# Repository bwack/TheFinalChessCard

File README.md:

# TheFinalChessCard Replica

TheFinalChessCard for C64/C128, replicated using SprintLayout. Here are the sprint and gerber files.

The scanned images are from the World of Jani blog article about this card. See also the forum64.de threads.
- http://blog.worldofjani.com/?p=3460
- https://www.forum64.de/index.php?thread/73757-the-final-chesscard/

## preview images from SprintLayout

# The Replica 1.0 prototype

The PCB Rev 1.0 has been [prototyped by Amon_RA on twitter](https://twitter.com/Amon_RA/status/1220659582181224448 "The tweets"). Thank you so much! Here are two images from his setup:

Image 1            |  Image 2
:-------------------------:|:-------------------------:
  |  

The Rev 1.0 had a grounded READ pin near the top edge. To find it look at the 74LS32 closest to the CPU, pin 8. If you have Rev 1.0, cut this trace betwen pin8 and GND at top edge. This is fixed in Rev 1.1

I would also like to thank the work by lvr for the schematics draft he posted in [a forum64.de thread](https://www.forum64.de/index.php?thread/73757-the-final-chesscard/&postID=1139564#post1139564 "A draft of the schematics for TheFinalChessCart"). With this schematic I was able to match my gerbers against a netlist generated from his schematics, and in this way the error in Rev 1.0 was easy to spot. The draft was very close to the layout. Thanks also to [@thilographie_de](https://twitter.com/thilographie_de) for hunting the error with me.

# Links

After doing the C64 KU-motherboard and the videoseries, I still hadn't shown my viewers how I went from images to gerber files. This is where I got the motivation for doing this TFCC replica. I made two videos. The first video got linked on Jani's website and also ended up in an article about it on hackaday called [Reverse Engineer PCBs With SprintLayout](https://hackaday.com/2019/12/31/reverse-engineer-pcbs-with-sprintlayout/). :-)

## Change log

* 2020-01-25 Rev 1.1:
  * pin 8 "READ" on 74LS32 (near CPU) was grounded. Removed GND.
  * A trace stopped too early before a via. Still connected. Fixed.
* 2019-12-31 Rev 1.0: Touched up traces on a finer grid. 45degree bends.
* shown in video: traced up. quick 90 degree bends

# TheFinalChessCard KiCad (modified replica)

The replica above I'd like to be .. a replica. Some changes are desired.
In this KiCad version we have moved two ICs back onto the grid. They were just too close for IC sockets.
A zener diode was also too close to the same ICs. The crystal touched some metal. The power rails were thin.
I have solved the changes in this version.
The schematics were drafted by lvr as mentioned above regarding the PCB Rev 1.0.

Gerbers are available. Look under the KiCad folder.

## Change log
The KiCad version branches off from the replica 1.1 board, hence why it is called 1.1.K1 where K is KiCad :)

Note that this version has never been prototype. Use at own risk if you decide to do so!

* 2020-01-26 Rev 1.1.K1:
  * Silkscreen artwork
  * Thicker power traces (0.63. -> 1mm)
  * Better space between two ICs. Moved some components to satisfy Cortyard errors.
  * New reset button. Standard 5x5mm push button.

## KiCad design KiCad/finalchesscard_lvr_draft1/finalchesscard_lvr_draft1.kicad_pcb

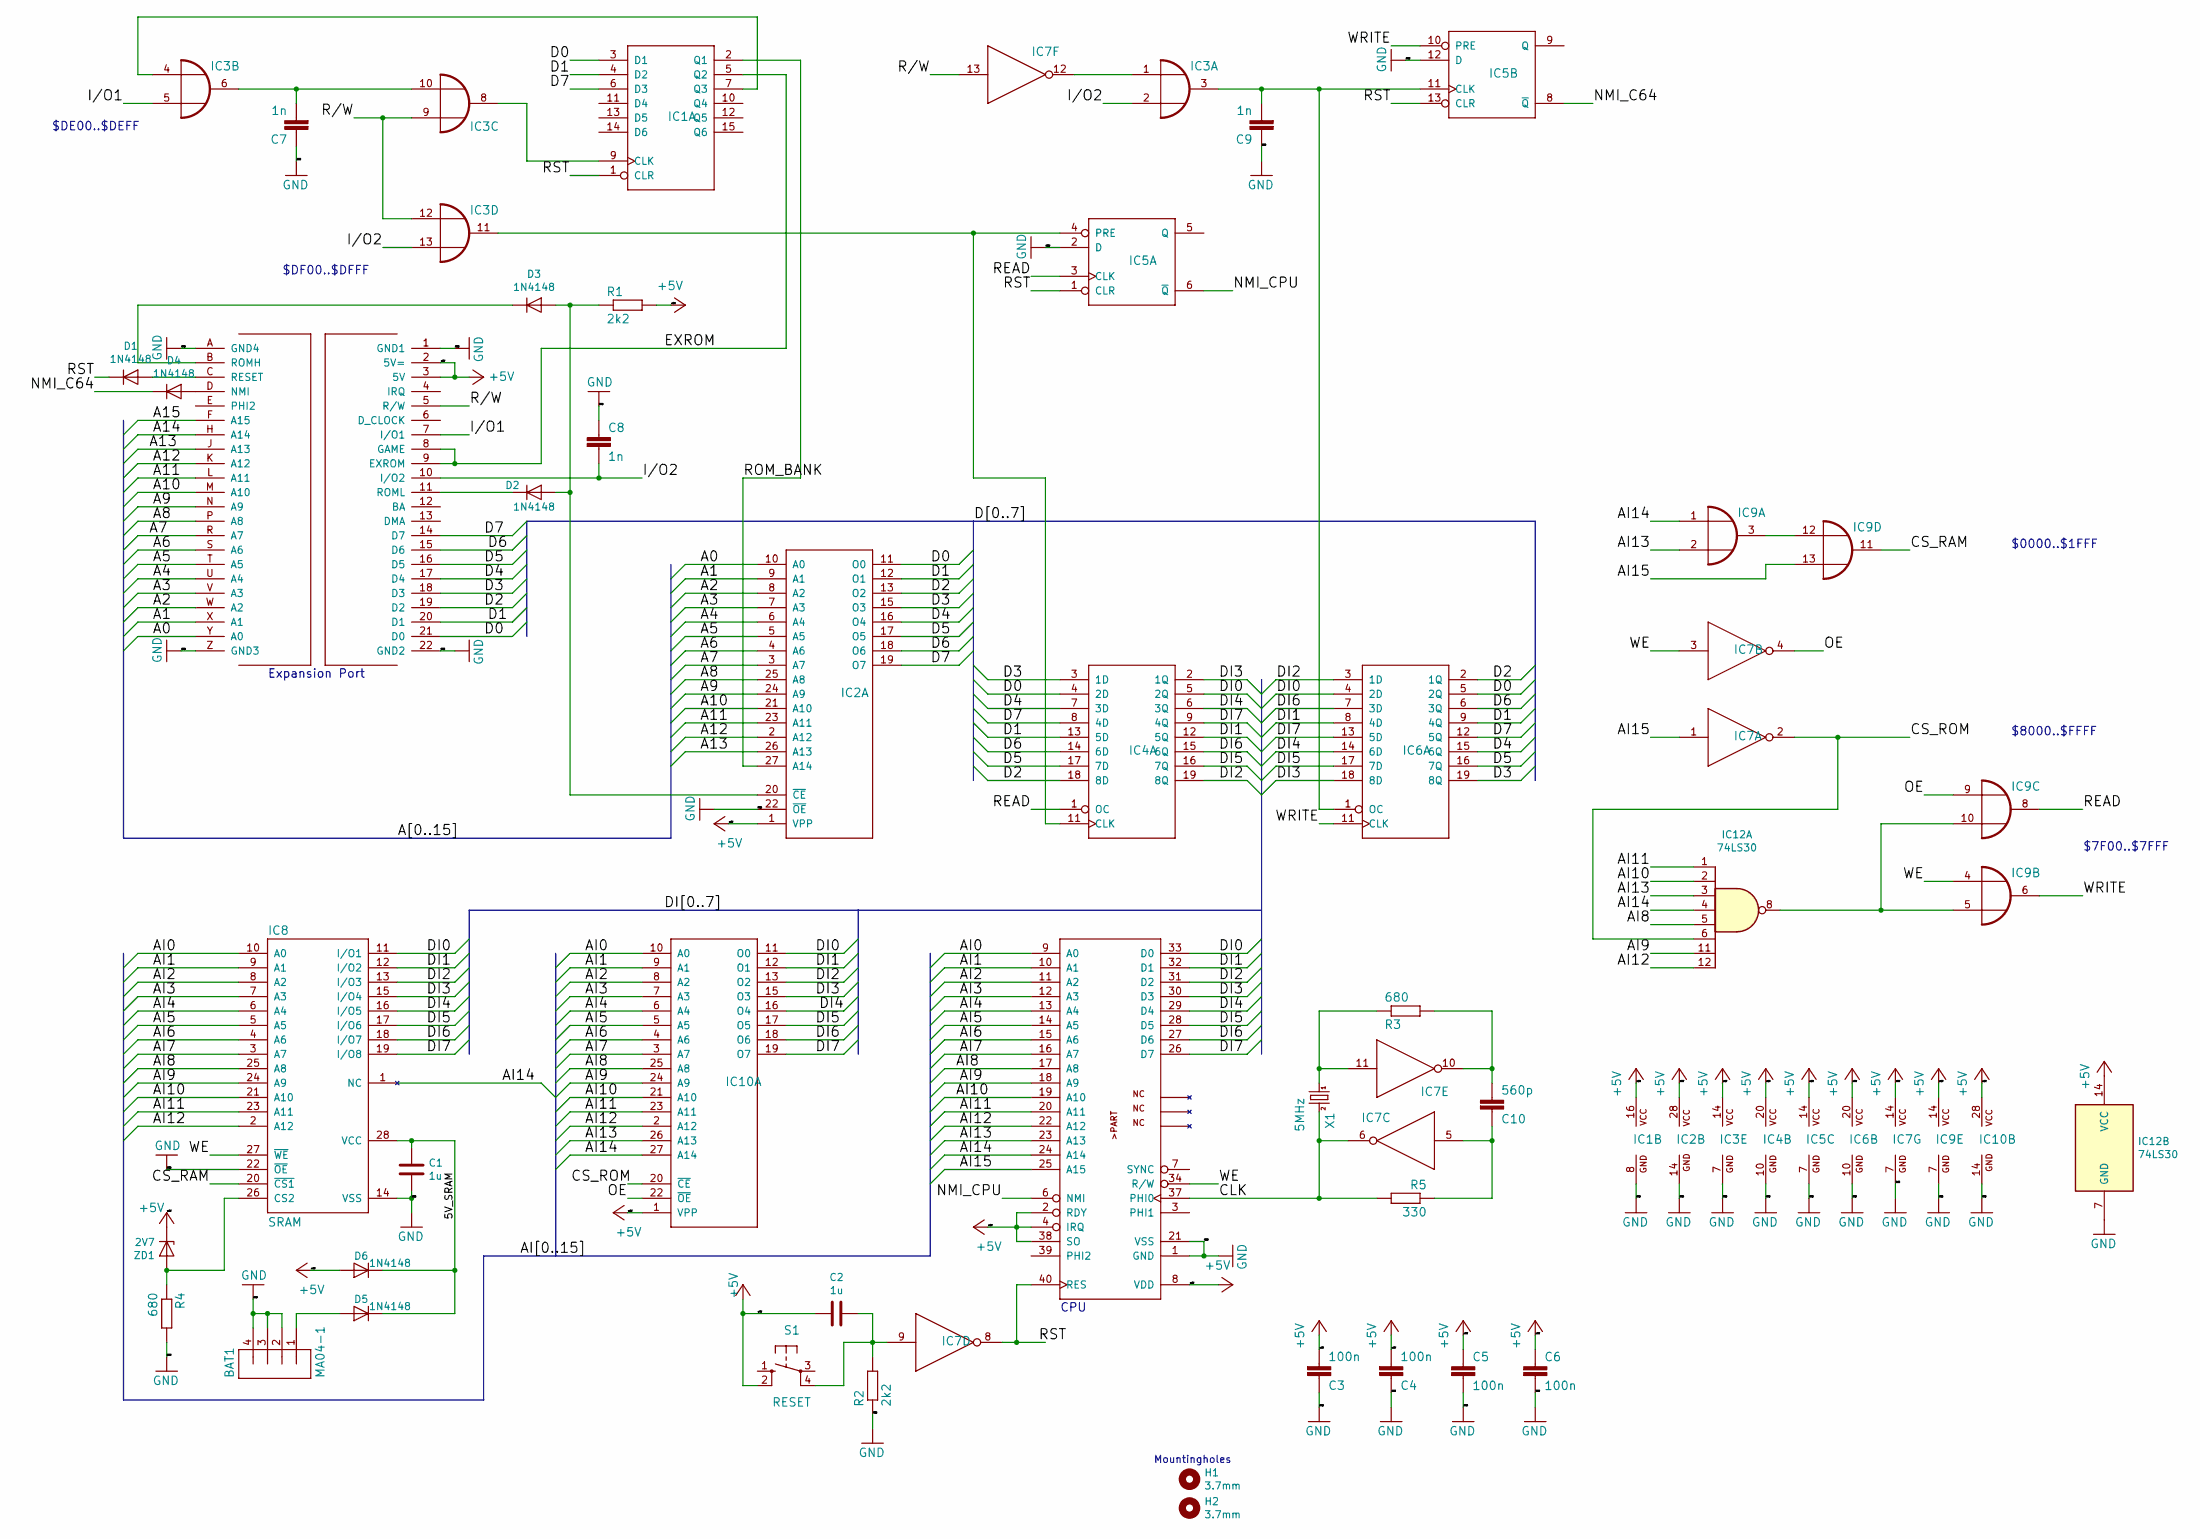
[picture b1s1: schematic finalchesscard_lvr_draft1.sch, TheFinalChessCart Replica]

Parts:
BAT1: MA04-1; PinHeader_1x04_P2.54mm_Vertical
C1: 1u; C_Rect_L7.0mm_W2.0mm_P5.00mm
C2: 1u; C_Rect_L4.0mm_W2.5mm_P2.50mm
C3, C4, C5, C6: 100n; C_Disc_D4.3mm_W1.9mm_P5.00mm
C7, C8, C9: 1n; C_Disc_D4.3mm_W1.9mm_P5.00mm
C10: 560p; C_Disc_D4.3mm_W1.9mm_P5.00mm
D1, D2, D3, D4: 1N4148; D_DO-34_SOD68_P10.16mm_Horizontal
D5, D6: 1N4148; D_DO-34_SOD68_P7.62mm_Horizontal
H1, H2: 3.7mm; MountingHole_3.7mm
IC1: 74174N; DIP-16_W7.62mm
IC2: ROM1; DIP-28_W15.24mm
IC3, IC9: 7432N; DIP-14_W7.62mm
IC4, IC6: 74374N; DIP-20_W7.62mm
IC5: 7474N; DIP-14_W7.62mm
IC7: 74LS04N; DIP-14_W7.62mm
IC8: SRAM; DIP-28_W15.24mm
IC10: ROM2; DIP-28_W15.24mm
IC11: 6502; DIP-40_W15.24mm
IC12: 74LS30; DIP-14_W7.62mm
R1, R2: 2k2; R_Axial_DIN0207_L6.3mm_D2.5mm_P10.16mm_Horizontal
R3: 680; R_Axial_DIN0207_L6.3mm_D2.5mm_P10.16mm_Horizontal
R4: 680; R_Axial_DIN0207_L6.3mm_D2.5mm_P15.24mm_Horizontal
R5: 330; R_Axial_DIN0207_L6.3mm_D2.5mm_P10.16mm_Horizontal
S1: RESET; SW_TH_Tactile_Omron_B3F-10xx
U$2: CARTRIDGE; C64_EXPANSION_PORT
X1: 5MHz; Crystal_HC49-U_Vertical
ZD1: 2V7; D_DO-34_SOD68_P7.62mm_Horizontal

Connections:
+5V: C2.2, C3.2, C4.2, C5.1, C6.1, D6.2 (A), IC1.16 (VCC), IC2.1 (VPP), IC2.28 (VCC), IC3.14 (VCC), IC4.20 (VCC), IC5.14 (VCC), IC6.20 (VCC), IC7.14 (VCC), IC9.14 (VCC), IC10.1 (VPP), IC10.28 (VCC), IC11.2 (RDY), IC11.4 (IRQ), IC11.8 (VDD), IC11.38 (SO), IC12.14 (VCC), R1.2, S1.2 (S1), U$2.2 (5V=), U$2.3 (5V), ZD1.1 (K)
/5V_SRAM: C1.1, D5.1 (K), D6.1 (K), IC8.28 (VCC)
/A0: IC2.10 (A0), U$2.Y (A0)
/A1: IC2.9 (A1), U$2.X (A1)
/A2: IC2.8 (A2), U$2.W (A2)
/A3: IC2.7 (A3), U$2.V (A3)
/A4: IC2.6 (A4), U$2.U (A4)
/A5: IC2.5 (A5), U$2.T (A5)
/A6: IC2.4 (A6), U$2.S (A6)
/A7: IC2.3 (A7), U$2.R (A7)
/A8: IC2.25 (A8), U$2.P (A8)
/A9: IC2.24 (A9), U$2.N (A9)
/A10: IC2.21 (A10), U$2.M (A10)
/A11: IC2.23 (A11), U$2.L (A11)
/A12: IC2.2 (A12), U$2.K (A12)
/A13: IC2.26 (A13), U$2.J (A13)
/A14: U$2.H (A14)
/A15: U$2.F (A15)
/AI0: IC8.10 (A0), IC10.10 (A0), IC11.9 (A0)
/AI1: IC8.9 (A1), IC10.9 (A1), IC11.10 (A1)
/AI2: IC8.8 (A2), IC10.8 (A2), IC11.11 (A2)
/AI3: IC8.7 (A3), IC10.7 (A3), IC11.12 (A3)
/AI4: IC8.6 (A4), IC10.6 (A4), IC11.13 (A4)
/AI5: IC8.5 (A5), IC10.5 (A5), IC11.14 (A5)
/AI6: IC8.4 (A6), IC10.4 (A6), IC11.15 (A6)
/AI7: IC8.3 (A7), IC10.3 (A7), IC11.16 (A7)
/AI8: IC8.25 (A8), IC10.25 (A8), IC11.17 (A8), IC12.5
/AI9: IC8.24 (A9), IC10.24 (A9), IC11.18 (A9), IC12.11
/AI10: IC8.21 (A10), IC10.21 (A10), IC11.19 (A10), IC12.2
/AI11: IC8.23 (A11), IC10.23 (A11), IC11.20 (A11), IC12.1
/AI12: IC8.2 (A12), IC10.2 (A12), IC11.22 (A12), IC12.12
/AI13: IC9.2 (I1), IC10.26 (A13), IC11.23 (A13), IC12.3
/AI14: IC8.1 (NC), IC9.1 (I0), IC10.27 (A14), IC11.24 (A14), IC12.4
/AI15: IC7.1 (I), IC9.13 (I1), IC11.25 (A15)
/CLK: IC7.6 (O), IC11.37 (PHI0), R5.2, X1.2
/CS_RAM: IC8.20 (~CS1), IC9.11 (O)
/CS_ROM: IC7.2 (O), IC10.20 (~CE), IC12.6
/D0: IC1.3 (D1), IC2.11 (O0), IC4.4 (2D), IC6.5 (2Q), U$2.21 (D0)
/D1: IC1.4 (D2), IC2.12 (O1), IC4.13 (5D), IC6.9 (4Q), U$2.20 (D1)
/D2: IC2.13 (O2), IC4.18 (8D), IC6.2 (1Q), U$2.19 (D2)
/D3: IC2.15 (O3), IC4.3 (1D), IC6.19 (8Q), U$2.18 (D3)
/D4: IC2.16 (O4), IC4.7 (3D), IC6.15 (6Q), U$2.17 (D4)
/D5: IC2.17 (O5), IC4.17 (7D), IC6.16 (7Q), U$2.16 (D5)
/D6: IC2.18 (O6), IC4.14 (6D), IC6.6 (3Q), U$2.15 (D6)
/D7: IC1.6 (D3), IC2.19 (O7), IC4.8 (4D), IC6.12 (5Q), U$2.14 (D7)
/DI0: IC4.5 (2Q), IC6.4 (2D), IC8.11 (I/O1), IC10.11 (O0), IC11.33 (D0)
/DI1: IC4.12 (5Q), IC6.8 (4D), IC8.12 (I/O2), IC10.12 (O1), IC11.32 (D1)
/DI2: IC4.19 (8Q), IC6.3 (1D), IC8.13 (I/O3), IC10.13 (O2), IC11.31 (D2)
/DI3: IC4.2 (1Q), IC6.18 (8D), IC8.15 (I/O4), IC10.15 (O3), IC11.30 (D3)
/DI4: IC4.6 (3Q), IC6.14 (6D), IC8.16 (I/O5), IC10.16 (O4), IC11.29 (D4)
/DI5: IC4.16 (7Q), IC6.17 (7D), IC8.17 (I/O6), IC10.17 (O5), IC11.28 (D5)
/DI6: IC4.15 (6Q), IC6.7 (3D), IC8.18 (I/O7), IC10.18 (O6), IC11.27 (D6)
/DI7: IC4.9 (4Q), IC6.13 (5D), IC8.19 (I/O8), IC10.19 (O7), IC11.26 (D7)
/EXROM: IC1.5 (Q2), U$2.8 (GAME), U$2.9 (EXROM)
/I/O1: IC3.5 (I1), U$2.7 (I/O1)
/I/O2: C8.2, IC3.2 (I1), IC3.13 (I1), U$2.10 (I/O2)
/NMI_C64: D4.1 (K), IC5.8 (~Q)
/NMI_CPU: IC5.6 (~Q), IC11.6 (NMI)
/OE: IC7.4 (O), IC9.9 (I0), IC10.22 (~OE)
/R/W: IC3.9 (I0), IC3.12 (I0), IC7.13 (I), U$2.5 (R/W)
/READ: IC4.1 (OC), IC5.3 (CLK), IC9.8 (O)
/ROM_BANK: IC1.2 (Q1), IC2.27 (A14)
/RST: D1.1 (K), IC1.1 (CLR), IC5.1 (CLR), IC5.13 (CLR), IC7.8 (O), IC11.40 (RES)
/WE: IC7.3 (I), IC8.27 (~WE), IC9.4 (I0), IC11.34 (R/W)
/WRITE: IC5.10 (PRE), IC6.11 (CLK), IC9.6 (O)
GND: BAT1.2, BAT1.3, BAT1.4, C1.2, C3.1, C4.1, C5.2, C6.2, C7.1, C8.1, C9.1, IC1.8 (GND), IC2.14 (GND), IC2.22 (~OE), IC3.7 (GND), IC4.10 (GND), IC5.2 (D), IC5.7 (GND), IC5.12 (D), IC6.10 (GND), IC7.7 (GND), IC8.14 (VSS), IC8.22 (~OE), IC9.7 (GND), IC10.14 (GND), IC11.1 (GND), IC11.21 (VSS), IC12.7 (GND), R2.1, R4.2, U$2.1 (GND1), U$2.22 (GND2), U$2.A (GND4), U$2.Z (GND3)
unnamed: BAT1.1, D5.2 (A)
unnamed: C2.1, IC7.9 (I), R2.2, S1.4 (P1)
unnamed: C7.2, IC3.6 (O), IC3.10 (I1)
unnamed: C9.2, IC3.3 (O), IC5.11 (CLK), IC6.1 (OC)
unnamed: C10.1, IC7.5 (I), R5.1
unnamed: C10.2, IC7.10 (O), R3.2
unnamed: D1.2 (A), U$2.C (RESET)
unnamed: D2.1 (K), U$2.11 (ROML)
unnamed: D2.2 (A), D3.2 (A), IC2.20 (~CE), R1.1
unnamed: D3.1 (K), U$2.B (ROMH)
unnamed: D4.2 (A), U$2.D (NMI)
unnamed: IC1.7 (Q3), IC3.4 (I0)
unnamed: IC1.9 (CLK), IC3.8 (O)
unnamed: IC3.1 (I0), IC7.12 (O)
unnamed: IC3.11 (O), IC4.11 (CLK), IC5.4 (PRE)
unnamed: IC7.11 (I), R3.1, X1.1
unnamed: IC8.26 (CS2), R4.1, ZD1.2 (A)
unnamed: IC9.3 (O), IC9.12 (I0)
unnamed: IC9.5 (I1), IC9.10 (I1), IC12.8

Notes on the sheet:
$0000..$1FFF
$8000..$FFFF
$DE00..$DEFF
$DF00..$DFFF
Expansion Port
$7F00..$7FFF
CPU
Mountingholes

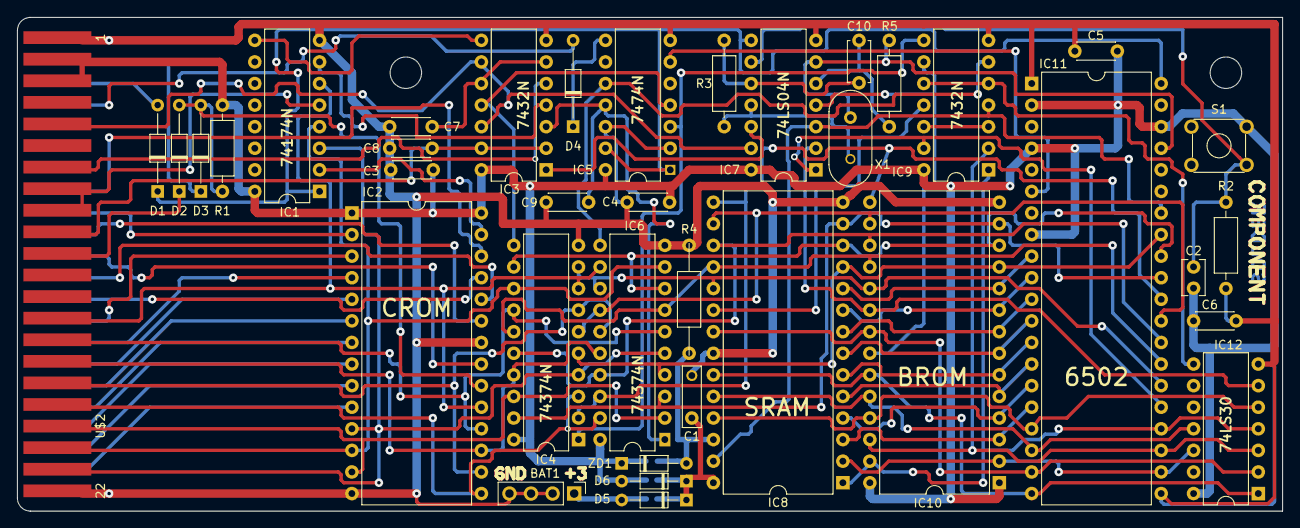
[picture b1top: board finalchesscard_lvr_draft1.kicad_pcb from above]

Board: 2 copper layers, 148.9 x 58.1 mm, 40 parts (0 on the bottom side), 83 nets.

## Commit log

2019-12-31 added soldermask
2020-01-25 Replica 1.1
    See readme
2020-01-25 Amon Ra's images
2020-01-26 Added KiCad project modified
2020-01-26 Images of the modified board
